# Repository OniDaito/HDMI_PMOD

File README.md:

# HDMI Compatible PMOD board for Arty A7

This is KiCAD project, complete with Gerbers, for a HDMI Compatible PMOD controller. Plug this into one of your PMOD sockets on your Arty A7 and you have a working HDMI compatible socket.

## Bill of Materials (BOM)

* Texas Instruments TPS61222DCKT Boost Convertor [RS Components Link](https://uk.rs-online.com/web/p/boost-converters/1627959)
* Inductor L1 4.7uH  - [Mouser Link](https://www.mouser.co.uk/ProductDetail/TDK/TMS322512ALM-4R7MTAA?qs=rQFj71Wb1eW%2Fk6%252BkfkK6Ug%3D%3D&countryCode=GB&currencyCode=GBP)
* Capacitors C1, C2 10uF 0805/2012 - [Mouser Link](https://www.mouser.co.uk/ProductDetail/KYOCERA-AVX/0805YC106KAT2A?qs=3HJ2avRr9PKwMzeRMZhF2g%3D%3D&countryCode=GB&currencyCode=GBP)
* HDMI Socket -  [Mouser Link](https://www.mouser.co.uk/ProductDetail/Molex/208658-1001?qs=B6kkDfuK7%2FCPiHHdkGL5VQ%3D%3D&countryCode=GB&currencyCode=GBP)
* Right Angle Molex 2 x 6 socket -  [Mouser Link](https://www.mouser.co.uk/ProductDetail/Molex/90122-0126?qs=PvP5v7Eimsm0iCqn6boA0w%3D%3D&countryCode=GB&currencyCode=GBP)
* This board.

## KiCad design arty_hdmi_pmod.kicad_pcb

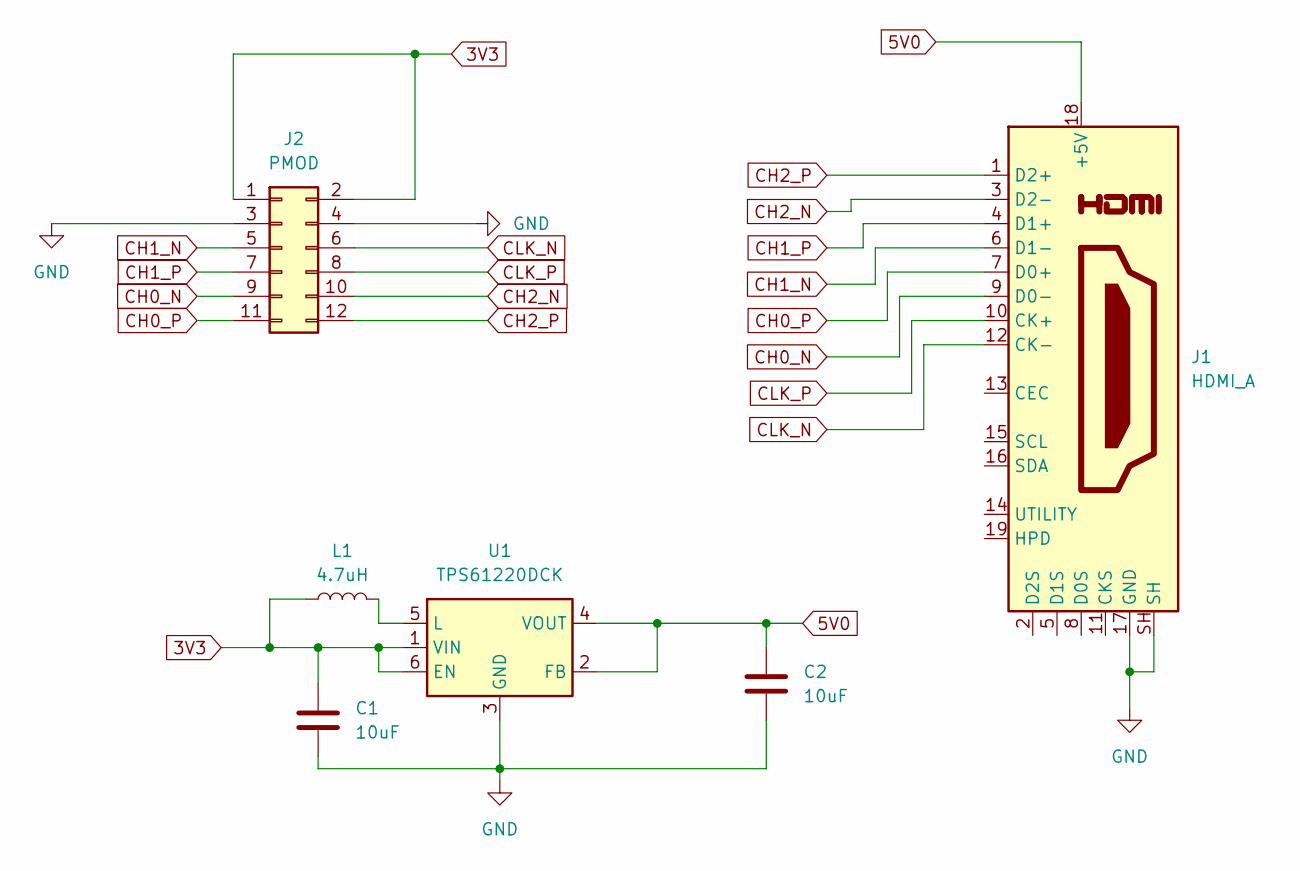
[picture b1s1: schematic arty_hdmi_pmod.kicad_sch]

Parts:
C1, C2: 10uF; C_0805_2012Metric_Pad1.18x1.45mm_HandSolder
J1: HDMI_A; HDMI_A_Molex_208658-1001_Horizontal
J2: PMOD; PinHeader_2x06_P2.54mm_Vertical
L1: 4.7uH; L_Coilcraft_XxL4040
U1: TPS61220DCK; Texas_R-PDSO-G6

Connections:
3V3: C1.1, J2.1, J2.2, L1.1, U1.1 (VIN), U1.6 (EN)
5V0: C2.1, J1.18 (+5V), U1.2 (FB), U1.4 (VOUT)
CH0_N: J1.9 (D0-), J2.9
CH0_P: J1.7 (D0+), J2.11
CH1_N: J1.6 (D1-), J2.5
CH1_P: J1.4 (D1+), J2.7
CH2_N: J1.3 (D2-), J2.10
CH2_P: J1.1 (D2+), J2.12
CLK_N: J1.12 (CK-), J2.6
CLK_P: J1.10 (CK+), J2.8
GND: C1.2, C2.2, J1.17 (GND), J1.SH, J2.3, J2.4, U1.3 (GND); also elsewhere on the board
unnamed: L1.2, U1.5 (L)

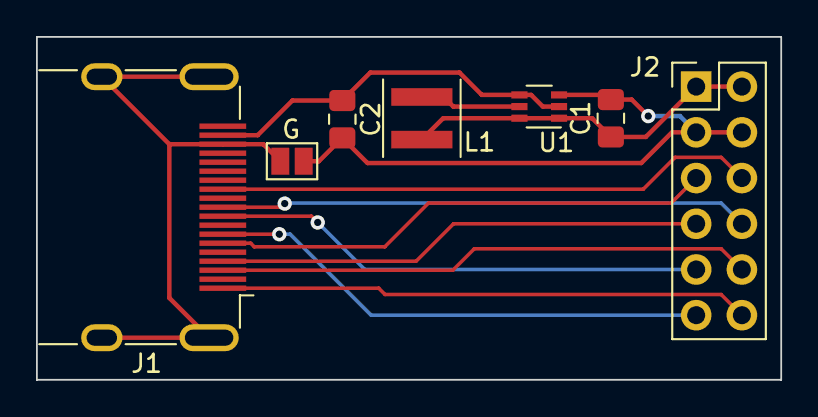
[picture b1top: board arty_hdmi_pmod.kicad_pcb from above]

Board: 2 copper layers, 41.4 x 19.1 mm, 7 parts (0 on the bottom side), 12 nets.

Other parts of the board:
G: SolderJumper-2_P1.3mm_Open_Pad1.0x1.5mm

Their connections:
GND: G.1, G.2; also elsewhere on the board
